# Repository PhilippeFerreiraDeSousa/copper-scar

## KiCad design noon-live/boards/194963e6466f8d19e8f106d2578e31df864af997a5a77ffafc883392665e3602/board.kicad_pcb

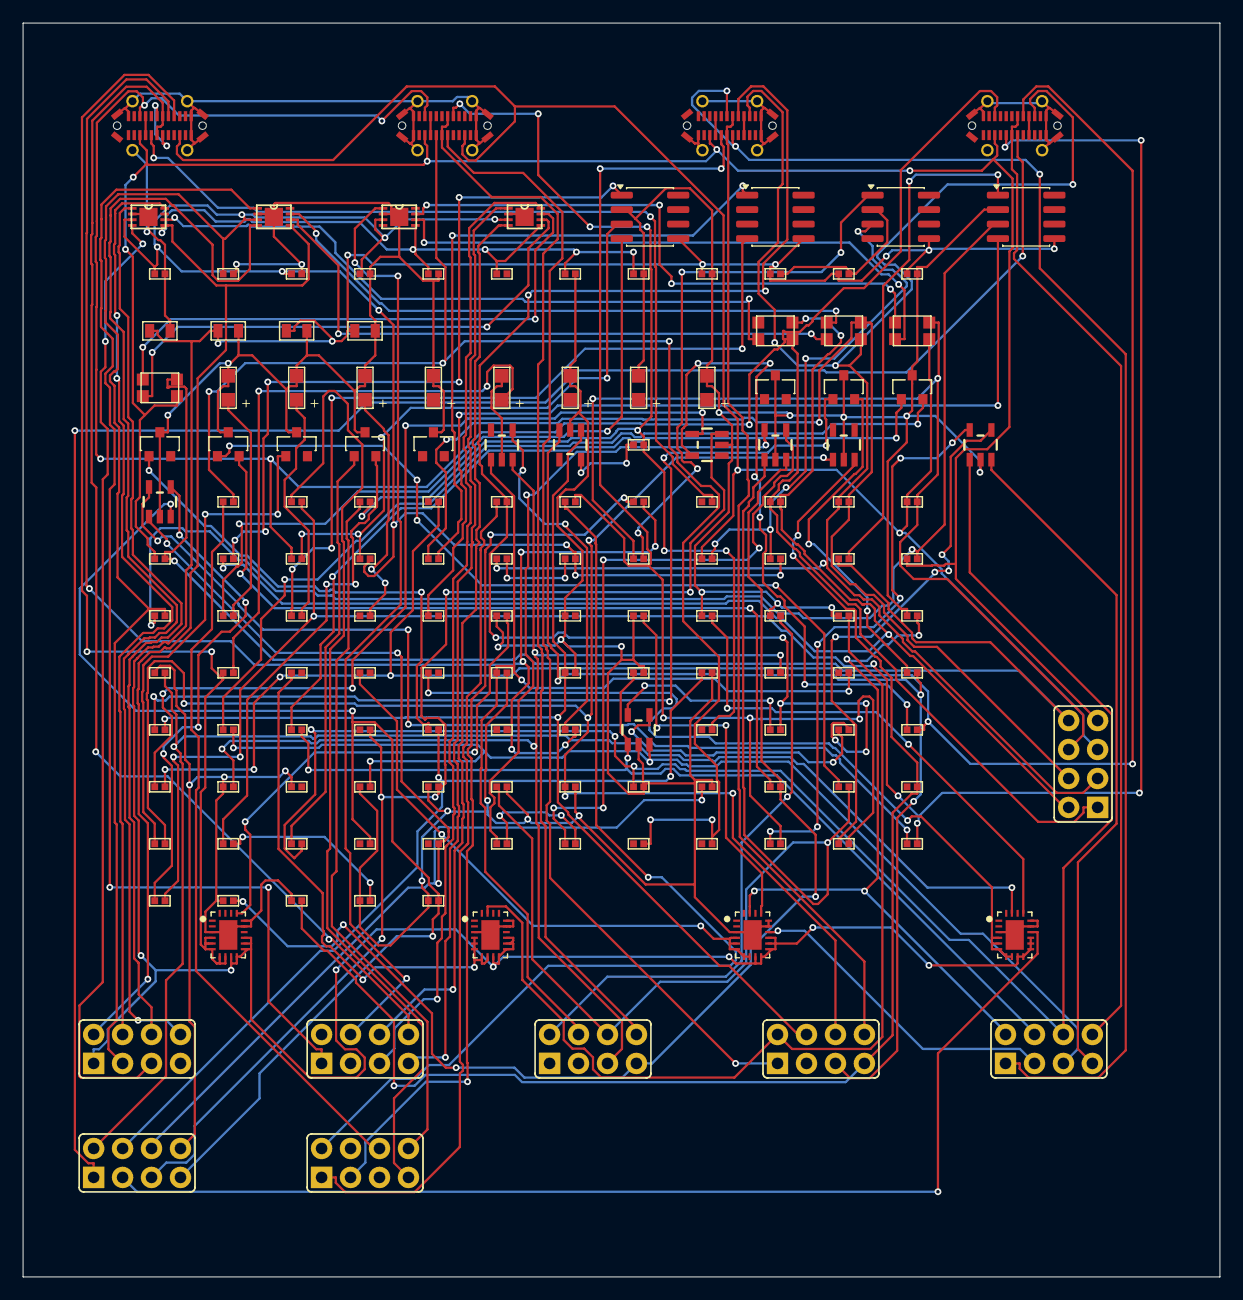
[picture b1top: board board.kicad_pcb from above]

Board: 2 copper layers, 105.0 x 110.0 mm, 156 parts (0 on the bottom side), 140 nets.

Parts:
C38, C39, C40, C41, C42, C43, C44, C45, C46, C47, C48, C49: 100nF; 0402-C
C50, C51, C52, C53: 10u; 0805-C
J4, J101, J102, J103, J104, J105, J106, J107: HEADER_2x04_2.54mm_POPULATED; 2X04
J5, J6, J7, J8: USB-C-FEMALEGCT; USB-C-FEMALE-VERT-GCT
L5, L6, L7, L8: ACT1210D_CHOKE; CHOKE-3.2X2.5
LED2: CAN0; CHIPLED
LED3: CAN1; CHIPLED
LED4: CAN2; CHIPLED
LED5: CAN3; CHIPLED
LED6, LED7, LED8, LED9: CH1_PWR; CHIPLED
LED10, LED11, LED12, LED13, LED14, LED15, LED16, LED17: LED-CC-GREEN-RED-AM23ESG; SOT23-3
Q2, Q3, Q4, Q5, Q6, Q7, Q8, Q9: NFET-DUAL-COMMON-SOURCE-QS5K2; SOT23-5
R13, R14, R15, R16, R17, R18, R19, R20, R52, R55, R58, R61: 100k; 0402-R
R46, R47, R48, R49: 60; 0402-R
R50, R51, R53, R54, R56, R57, R59, R60, R78, R79, R80, R81, R98, R99, R100, R101, R102, R103, R104, R105, R122, R123, R124, R125: 10k; 0402-R
R62, R63, R64, R65: 2k7; 0402-R
R66, R67, R68, R69: 28k; 0402-R
R70, R71, R72, R73: 33k; 0402-R
R74, R75, R76, R77: 3k3; 0402-R
R82, R83, R84, R85, R86, R87, R88, R89, R91, R93, R95, R97, R106, R107, R108, R109, R110, R111, R112, R113, R115, R117, R119, R121: 100; 0402-R
R90, R92, R94, R96, R114, R116, R118, R120: 1k; 0402-R
U5, U6, U7, U8: MCP2542FDT-E/MNY; TDFN8_2X3MC_MCH
U9, U10, U11, U12: NCS20071XV; SOIC-8_3.9x4.9mm_P1.27mm
U13, U14, U15, U16: TPS25942; WQFN20

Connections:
+3V3: C42.1, C43.1, C44.1, C45.1, J101.2, U5.5 (VIO), U6.5 (VIO), U7.5 (VIO), U8.5 (VIO)
+5V: C38.1, C39.1, C40.1, C41.1, J101.3, R52.2, R55.2, R58.2, R61.2, U5.3 (VDD), U6.3 (VDD), U7.3 (VDD), U8.3 (VDD)
+12V: C46.1, C47.1, C48.1, C49.1, C50.1, C51.1, C52.1, C53.1, J101.1, U9.5 (V+), U10.5 (V+), U11.5 (V+), U12.5 (V+), U13.9 (VIN), U13.10 (VIN), U13.11 (VIN), U13.12 (VIN), U13.13 (VIN), U14.9 (VIN), U14.10 (VIN), U14.11 (VIN), U14.12 (VIN), U14.13 (VIN), U15.9 (VIN), U15.10 (VIN), U15.11 (VIN), U15.12 (VIN), U15.13 (VIN), U16.9 (VIN), U16.10 (VIN), U16.11 (VIN), U16.12 (VIN), U16.13 (VIN)
CAN0_EN: J101.4, U5.8 (STBY)
CAN0_H: J4.2, J5.A2 (TX1+), J6.A2 (TX1+), J7.A2 (TX1+), J8.A2 (TX1+), L5.4, R46.2, R50.1
CAN0_L: J4.1, J5.A3 (TX1-), J6.A3 (TX1-), J7.A3 (TX1-), J8.A3 (TX1-), L5.3, R46.1, R51.1
CAN0_RX: J101.5, U5.4 (RXD)
CAN0_TX: J101.6, U5.1 (TXD)
CAN1_EN: J101.7, U6.8 (STBY)
CAN1_H: J4.4, J5.A11 (RX2+), J6.A11 (RX2+), J7.A11 (RX2+), J8.A11 (RX2+), L6.4, R47.2, R53.1
CAN1_L: J4.3, J5.A10 (RX2-), J6.A10 (RX2-), J7.A10 (RX2-), J8.A10 (RX2-), L6.3, R47.1, R54.1
CAN1_RX: J101.8, U6.4 (RXD)
CAN1_TX: J102.1, U6.1 (TXD)
CAN2_EN: J102.2, U7.8 (STBY)
CAN2_H: J4.6, J5.B2 (TX2+), J6.B2 (TX2+), J7.B2 (TX2+), J8.B2 (TX2+), L7.4, R48.2, R56.1
CAN2_L: J4.5, J5.B3 (TX2-), J6.B3 (TX2-), J7.B3 (TX2-), J8.B3 (TX2-), L7.3, R48.1, R57.1
CAN2_RX: J102.3, U7.4 (RXD)
CAN2_TX: J102.4, U7.1 (TXD)
CAN3_EN: J102.5, U8.8 (STBY)
CAN3_H: J4.8, J5.B11 (RX1+), J6.B11 (RX1+), J7.B11 (RX1+), J8.B11 (RX1+), L8.4, R49.2, R59.1
CAN3_L: J4.7, J5.B10 (RX1-), J6.B10 (RX1-), J7.B10 (RX1-), J8.B10 (RX1-), L8.3, R49.1, R60.1
CAN3_RX: J102.6, U8.4 (RXD)
CAN3_TX: J102.7, U8.1 (TXD)
CH1_D_N: J5.A7 (D-A), J5.B7 (D-B), J102.8
CH1_D_P: J5.A6 (D+A), J5.B6 (D+B), J103.1
CH1_IMON: J103.2, R70.2, U13.19 (IMON)
CH1_PWR_EN: J103.3, U13.14 (EN)
CH1_SBU1: J5.A8 (SBU1), R19.2, R90.2, R91.2
CH1_SBU1_IGN: J103.4, Q2.1 (G1), R78.1, R83.2
CH1_SBU1_RELAY: J103.5, Q2.3 (G2), R82.2, R98.2
CH1_SBU2: J5.B8 (SBU2), R20.2, R114.2, R115.2
CH1_SBU2_IGN: J103.6, Q6.1 (G1), R102.1, R107.2
CH1_SBU2_RELAY: J103.7, Q6.3 (G2), R106.2, R122.2
CH2_D_N: J6.A7 (D-A), J6.B7 (D-B), J103.8
CH2_D_P: J6.A6 (D+A), J6.B6 (D+B), J104.1
CH2_IMON: J104.2, R71.2, U14.19 (IMON)
CH2_PWR_EN: J104.3, U14.14 (EN)
CH2_SBU1: J6.A8 (SBU1), R15.2, R92.2, R93.2
CH2_SBU1_IGN: J104.4, Q3.1 (G1), R79.1, R85.2
CH2_SBU1_RELAY: J104.5, Q3.3 (G2), R84.2, R99.2
CH2_SBU2: J6.B8 (SBU2), R13.2, R116.2, R117.2
CH2_SBU2_IGN: J104.6, Q7.1 (G1), R103.1, R109.2
CH2_SBU2_RELAY: J104.7, Q7.3 (G2), R108.2, R123.2
CH3_D_N: J7.A7 (D-A), J7.B7 (D-B), J104.8
CH3_D_P: J7.A6 (D+A), J7.B6 (D+B), J105.1
CH3_IMON: J105.2, R72.2, U15.19 (IMON)
CH3_PWR_EN: J105.3, U15.14 (EN)
CH3_SBU1: J7.A8 (SBU1), R17.2, R94.2, R95.2
CH3_SBU1_IGN: J105.4, Q4.1 (G1), R80.1, R87.2
CH3_SBU1_RELAY: J105.5, Q4.3 (G2), R86.2, R100.2
CH3_SBU2: J7.B8 (SBU2), R18.2, R118.2, R119.2
CH3_SBU2_IGN: J105.6, Q8.1 (G1), R104.1, R111.2
CH3_SBU2_RELAY: J105.7, Q8.3 (G2), R110.2, R124.2
CH4_D_N: J8.A7 (D-A), J8.B7 (D-B), J105.8
CH4_D_P: J8.A6 (D+A), J8.B6 (D+B), J106.1
CH4_IMON: J106.2, R73.2, U16.19 (IMON)
CH4_PWR_EN: J106.3, U16.14 (EN)
CH4_SBU1: J8.A8 (SBU1), R16.2, R96.2, R97.2
CH4_SBU1_IGN: J106.4, Q5.1 (G1), R81.1, R89.2
CH4_SBU1_RELAY: J106.5, Q5.3 (G2), R88.2, R101.2
CH4_SBU2: J8.B8 (SBU2), R14.2, R120.2, R121.2
CH4_SBU2_IGN: J106.6, Q9.1 (G1), R105.1, R113.2
CH4_SBU2_RELAY: J106.7, Q9.3 (G2), R112.2, R125.2
GND: C38.2, C39.2, C40.2, C41.2, C42.2, C43.2, C44.2, C45.2, C46.2, C47.2, C48.2, C49.2, C50.2, C51.2, C52.2, C53.2, J5.A1 (GND), J5.A12 (GND), J5.B1 (GND), J5.B12 (GND), J5.S1 (SHIELDA), J5.S2 (SHIELDA), J5.S3 (SHIELDA), J5.S4 (SHIELDA), J5.S11 (SHIELDB), J5.S12 (SHIELDB), J5.S13 (SHIELDB), J5.S14 (SHIELDB), J6.A1 (GND), J6.A12 (GND), J6.B1 (GND), J6.B12 (GND), J6.S1 (SHIELDA), J6.S2 (SHIELDA), J6.S3 (SHIELDA), J6.S4 (SHIELDA), J6.S11 (SHIELDB), J6.S12 (SHIELDB), J6.S13 (SHIELDB), J6.S14 (SHIELDB), J7.A1 (GND), J7.A12 (GND), J7.B1 (GND), J7.B12 (GND), J7.S1 (SHIELDA), J7.S2 (SHIELDA), J7.S3 (SHIELDA), J7.S4 (SHIELDA), J7.S11 (SHIELDB), J7.S12 (SHIELDB), J7.S13 (SHIELDB), J7.S14 (SHIELDB), J8.A1 (GND), J8.A12 (GND), J8.B1 (GND), J8.B12 (GND), J8.S1 (SHIELDA), J8.S2 (SHIELDA), J8.S3 (SHIELDA), J8.S4 (SHIELDA), J8.S11 (SHIELDB), J8.S12 (SHIELDB), J8.S13 (SHIELDB), J8.S14 (SHIELDB), J106.8, LED2.C, LED3.C, LED4.C, LED5.C, LED6.C, LED7.C, LED8.C, LED9.C, LED10.3 (C), LED11.3 (C), LED12.3 (C), LED13.3 (C), LED14.3 (C), LED15.3 (C), LED16.3 (C), LED17.3 (C), Q2.2 (S), Q3.2 (S), Q4.2 (S), Q5.2 (S), Q6.2 (S), Q7.2 (S), Q8.2 (S), Q9.2 (S), R66.1, R67.1, R68.1, R69.1, R70.1, R71.1, R72.1, R73.1, R78.2, R79.2, R80.2, R81.2, R98.1, R99.1, R100.1, R101.1, R102.2, R103.2, R104.2, R105.2, R122.1, R123.1, R124.1, R125.1, U5.2 (VSS), U5.PAD (EPAD), U6.2 (VSS), U6.PAD (EPAD), U7.2 (VSS), U7.PAD (EPAD), U8.2 (VSS), U8.PAD (EPAD), U9.2 (V-), U10.2 (V-), U11.2 (V-), U12.2 (V-), U13.3 (PGTH), U13.15 (OVP), U13.16 (GND), U13.PAD (GND), U14.3 (PGTH), U14.15 (OVP), U14.16 (GND), U14.PAD (GND), U15.3 (PGTH), U15.15 (OVP), U15.16 (GND), U15.PAD (GND), U16.3 (PGTH), U16.15 (OVP), U16.16 (GND), U16.PAD (GND)
unnamed: J5.A4 (VBUS), J5.A9 (VBUS), J5.B4 (VBUS), J5.B9 (VBUS), R74.1, U13.4 (VOUT), U13.5 (VOUT), U13.6 (VOUT), U13.7 (VOUT), U13.8 (VOUT)
unnamed: J6.A4 (VBUS), J6.A9 (VBUS), J6.B4 (VBUS), J6.B9 (VBUS), R75.1, U14.4 (VOUT), U14.5 (VOUT), U14.6 (VOUT), U14.7 (VOUT), U14.8 (VOUT)
unnamed: J7.A4 (VBUS), J7.A9 (VBUS), J7.B4 (VBUS), J7.B9 (VBUS), R76.1, U15.4 (VOUT), U15.5 (VOUT), U15.6 (VOUT), U15.7 (VOUT), U15.8 (VOUT)
unnamed: J8.A4 (VBUS), J8.A9 (VBUS), J8.B4 (VBUS), J8.B9 (VBUS), R77.1, U16.4 (VOUT), U16.5 (VOUT), U16.6 (VOUT), U16.7 (VOUT), U16.8 (VOUT)
unnamed: LED2.A, R62.2
unnamed: LED3.A, R63.2
unnamed: LED4.A, R64.2
unnamed: LED5.A, R65.2
unnamed: LED6.A, R74.2
unnamed: LED7.A, R75.2
unnamed: LED8.A, R76.2
unnamed: LED9.A, R77.2
unnamed: LED10.2 (AG), R82.1
unnamed: LED10.1 (AR), R83.1
unnamed: LED11.2 (AG), R84.1
unnamed: LED11.1 (AR), R85.1
unnamed: LED12.2 (AG), R86.1
unnamed: LED12.1 (AR), R87.1
unnamed: LED13.2 (AG), R88.1
unnamed: LED13.1 (AR), R89.1
unnamed: LED14.2 (AG), R106.1
unnamed: LED14.1 (AR), R107.1
unnamed: LED15.2 (AG), R108.1
unnamed: LED15.1 (AR), R109.1
unnamed: LED16.2 (AG), R110.1
unnamed: LED16.1 (AR), R111.1
unnamed: LED17.2 (AG), R112.1
unnamed: LED17.1 (AR), R113.1
unnamed: Q2.5 (D1), R90.1
unnamed: Q2.4 (D2), R91.1
unnamed: Q3.5 (D1), R92.1
unnamed: Q3.4 (D2), R93.1
unnamed: Q4.5 (D1), R94.1
unnamed: Q4.4 (D2), R95.1
unnamed: Q5.5 (D1), R96.1
unnamed: Q5.4 (D2), R97.1
unnamed: Q6.5 (D1), R114.1
unnamed: Q6.4 (D2), R115.1
unnamed: Q7.5 (D1), R116.1
unnamed: Q7.4 (D2), R117.1
unnamed: Q8.5 (D1), R118.1
unnamed: Q8.4 (D2), R119.1
unnamed: Q9.5 (D1), R120.1
unnamed: Q9.4 (D2), R121.1
unnamed: R62.1, U9.4
unnamed: R63.1, U10.4
unnamed: R64.1, U11.4
unnamed: R65.1, U12.4
unnamed: J107.1, R17.1
unnamed: J107.2, R18.1
unnamed: J107.3, R19.1
unnamed: J107.4, R20.1
unnamed: J107.6, R13.1
unnamed: J107.7, R14.1
unnamed: J107.8, R15.1
unnamed: J107.5, R16.1
unnamed: L5.1, U5.7 (CANH)
unnamed: L5.2, U5.6 (CANL)
unnamed: L6.1, U6.7 (CANH)
unnamed: L6.2, U6.6 (CANL)
unnamed: L7.1, U7.7 (CANH)
unnamed: L7.2, U7.6 (CANL)
unnamed: L8.1, U8.7 (CANH)
unnamed: L8.2, U8.6 (CANL)
unnamed: R50.2, U9.1 (+)
unnamed: R51.2, R52.1, U9.3 (-)
unnamed: R53.2, U10.1 (+)
unnamed: R54.2, R55.1, U10.3 (-)
unnamed: R56.2, U11.1 (+)
unnamed: R57.2, R58.1, U11.3 (-)
unnamed: R59.2, U12.1 (+)
unnamed: R60.2, R61.1, U12.3 (-)
unnamed: R66.2, U13.17 (ILIM)
unnamed: R67.2, U14.17 (ILIM)
unnamed: R68.2, U15.17 (ILIM)
unnamed: R69.2, U16.17 (ILIM)
